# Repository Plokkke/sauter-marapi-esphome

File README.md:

# sauter-marapi-esphome

**Français** · [English](README.en.md)

Pilotez votre sèche-serviettes Sauter Marapi depuis Home Assistant, en gardant son écran et ses touches : une petite carte Wi-Fi se glisse sur le bus interne du radiateur.

> [!NOTE]
> **État du projet.** Le protocole du bus interne est décodé, et la carte MITM marche sur le radiateur (plaque d'essai, Wemos D1 mini, firmware ESPHome) : les touches et Home Assistant pilotent la carte de puissance. Restent la température, l'alimentation par la nappe, le circuit imprimé et le boîtier.

## Ce que ça permet

- **Suivre le radiateur** : consigne, Boost et arrêt réglés sur les touches, chauffe en cours.
- **Le régler depuis Home Assistant** : consigne, Boost (soufflerie), arrêt.
- **Garder l'appareil d'origine** : l'écran et les touches continuent de marcher comme avant ; le dernier qui parle, touche ou Home Assistant, a raison.
- **Rien à brancher sur le 230 V** : la carte s'alimente sur le 5 V de la nappe, comme le boîtier de commande.
- **Sans risque** : sans Home Assistant, les touches pilotent toujours le radiateur, et un Boost lancé par Home Assistant s'arrête de lui-même. Si la carte elle-même tombe en panne, le radiateur s'arrête (« Err 10 ») : il suffit de la débrancher et de reconnecter la nappe d'origine.

## Compatibilité

Étudié sur un **Sauter Marapi tactile 1750 W** (750 W de fluide et 1000 W de soufflerie), boîtier de commande `HM011 TD1N01 RAD`. Les sèche-serviettes et radiateurs du groupe Atlantic (Atlantic, Thermor, Sauter) qui affichent « Err 10 » quand leur nappe interne est débranchée utilisent probablement le même bus : à vérifier avec l'écoute de `discovery/`.

## Comment ça marche

Le radiateur a deux cartes, reliées par une nappe de trois fils (masse, 5 V, données) :

- le **boîtier de commande** (écran, touches tactiles) choisit la consigne, le mode et le Boost ;
- la **carte de puissance** chauffe le fluide et fait tourner la soufflerie, d'après sa propre sonde de température. Elle mène le dialogue : elle **appelle** le boîtier de commande plusieurs fois par seconde, et il répond par son état.

La carte coupe le fil de données et se place entre les deux, comme un intermédiaire (*man in the middle*). Elle a **son propre état** (arrêt, marche à une consigne, Boost), qu'elle donne à la carte de puissance en répondant à ses appels. Face au boîtier de commande, elle joue la carte de puissance : elle l'appelle et lit ses réponses. Les touches et Home Assistant changent cet état ; le dernier ordre gagne.

```mermaid
flowchart LR
  HA[Home Assistant] <-- Wi-Fi --> D1[Wemos D1 mini<br>ESPHome]
  CMD[Boîtier de commande<br>écran, touches] <-- données --> D1
  D1 <-- données --> PWR[Carte de puissance<br>fluide, soufflerie]
  PWR -. 5 V et masse, en direct .- CMD
  PWR -. 5 V .-> D1
```

**Limite** : le boîtier de commande n'accepte aucun ordre par le bus. Son écran affiche toujours ce qui a été réglé sur ses touches : un Boost lancé par Home Assistant ne s'y voit pas.

## Le bus interne en bref

Le détail, trame par trame, est dans [`knowledge/linap.md`](knowledge/linap.md).

- Un seul fil de données, **9 600 bauds, 7 bits et parité impaire**. Les trames font **5 octets** : un en-tête, 3 octets de données, puis leur XOR.
- La carte de puissance envoie `75`, `C7` et `61` en boucle (cycle de 305 ms). Après `75` et `C7`, elle envoie l'octet `46` seul : c'est l'appel. Le boîtier de commande répond **dans le bit qui suit**, par 3 octets et la somme de contrôle :

| Réponse à `46` | Sens |
|---|---|
| `B0 cc 80` | en marche, consigne = `cc` sans son bit 7, divisé par 2 |
| `38 80 80` | Boost |
| `80 80 80` | arrêt |

- La carte de puissance donne son état dans `C7` : `80 E0 38` au repos, `01 E0 38` en chauffe, `83 E0 98` en Boost, `80 E0 40` à l'arrêt.
- **La carte de puissance obéit à quiconque répond à temps** à ses appels. **Le boîtier de commande ne se laisse pas piloter** : il ne répond qu'aux appels `46` et `70`, et aucune des quelque 280 trames essayées n'a changé sa consigne ni son écran.

## La découverte du protocole

Aucune documentation n'existe sur ce bus. Il a été décodé avec un **Wemos D1 mini** branché sur la nappe, en trois étapes. Les firmwares, le schéma du banc et les outils sont dans [`discovery/`](discovery/README.md).

| Étape | L'ESP… | Résultat |
|---|---|---|
| 1. Écoute | écoute la nappe entre les deux cartes | format des trames, consigne, Boost, arrêt |
| 2. Fausse carte de puissance | appelle le boîtier de commande seul, sur table, sans secteur | il répond et donne tout ce qu'on fait sur ses touches, mais n'accepte aucun ordre |
| 3. Fausse carte de commande | répond à la carte de puissance, sur le radiateur | elle suit la consigne, le Boost et l'arrêt |

> [!WARNING]
> **Le bus interne est au potentiel du secteur.** Pendant les essais sur le radiateur, l'ESP flotte à ce potentiel : alimentation de laboratoire à sortie flottante, pilotage en Wi-Fi uniquement, jamais d'USB ni d'appareil relié à la terre. Couper le disjoncteur avant de toucher au montage. En cas de doute, faites appel à un électricien.

## Le matériel

> [!NOTE]
> En cours : la plaque d'essai ([`hardware/`](hardware/README.md)) marche sur le radiateur ; reste le circuit imprimé ([backlog](knowledge/backlog.md)).

Ce qui ne changera pas :

- **Un Wemos D1 mini** (ESP8266), firmware ESPHome avec un composant en C++ : la réponse aux appels part de nos propres interruptions. Son antenne imprimée tient la liaison sur le radiateur, là où un ESP32-C3 super mini la perdait.
- **Alimentée par la nappe**, en principe : le 5 V de la carte de puissance tient ≈ 160 mA en tout, et un D1 mini avec le boîtier de commande en prend ≈ 120 (VCC à 5,11 V, démarrages du radiateur et Boost validés pendant la découverte). Reste à le confirmer avec la carte MITM, essayée jusqu'ici sur une alimentation de labo. Un condensateur de 470 µF près de l'ESP absorbe les pointes du Wi-Fi.
- **Sur chaque voie**, le montage du banc : un pont diviseur pour lire DATA, un transistor NPN pour la tirer à la masse.
- **Toute la carte est au potentiel du secteur**, comme le boîtier de commande : elle doit être entièrement enfermée, sans rien de touchable, et se mettre à jour par Wi-Fi seulement.

## Firmware

Le firmware de la carte est une configuration **ESPHome** pour le D1 mini, avec un composant en C++, dans [`firmware/`](firmware/README.md) : logique des trames testée sur ordinateur, réponse aux appels sur interruption ; Wi-Fi, API Home Assistant et OTA par ESPHome.

```sh
uv tool install esphome
cp discovery/esphome/secrets.example.yaml discovery/esphome/secrets.yaml   # Wi-Fi, clé API, mot de passe OTA
firmware/tests/run.sh
esphome run firmware/sauter-marapi.yaml        # premier flash en USB, avant tout câblage ; ensuite OTA
```

Les firmwares du banc, eux, sont des configurations ESPHome pour D1 mini, dans `discovery/` :

```sh
esphome run discovery/1-sniffer/linap-sniffer.yaml       # premier flash en USB, avant tout câblage
esphome logs discovery/1-sniffer/linap-sniffer.yaml | discovery/tools/decode.py
```

## Dans Home Assistant

Par l'intégration ESPHome (détail : [`firmware/README.md`](firmware/README.md)) :

| Entité | Usage |
|---|---|
| Mode | `off`, `on`, `boost` : l'état de la carte, changé par les touches ou par Home Assistant |
| Setpoint | la consigne |
| Power board, Heating | ce que fait la carte de puissance : attente, chauffe, Boost, arrêt |
| Boost duration | durée d'un Boost lancé par Home Assistant (30 min par défaut) |

Le dernier ordre gagne : un ordre de Home Assistant remplace celui des touches, et le prochain changement fait aux touches le remplace à son tour. Au démarrage, la carte reprend l'état enregistré.

Le boîtier de commande n'envoie que sa consigne effective : en Éco, Home Assistant voit la consigne Éco, sans savoir que c'est l'Éco.

## Limites connues

- **Écran non synchronisé** : ce que Home Assistant impose n'apparaît pas à l'écran.
- **Pas de température** pour l'instant : la carte de puissance a sa sonde, et une capture longue cherche dans quelle trame passe la mesure.
- **Garantie** : ouvrir le boîtier de commande fait perdre la garantie (2 ans).

## Pour aller plus loin

- [`knowledge/linap.md`](knowledge/linap.md) : le bus interne, trame par trame.
- [`knowledge/architecture.md`](knowledge/architecture.md) : rôle de la carte, solution retenue, pistes écartées, sécurité.
- [`knowledge/backlog.md`](knowledge/backlog.md) : ce qui reste à faire.
- `knowledge/manuals/` : notice Sauter.

---

**Mots-clés** : Sauter Marapi tactile, sèche-serviettes soufflant, radiateur électrique, Groupe Atlantic, Thermor, Atlantic, bus interne, liaison Linap, Err 10, man in the middle, rétro-ingénierie, ESPHome, composant externe C++, Home Assistant, domotique, ESP8266, Wemos D1 mini, boîtier de commande `HM011 TD1N01 RAD`, `74 60 5004`, STM32F091CCT6, circuit imprimé KiCad.

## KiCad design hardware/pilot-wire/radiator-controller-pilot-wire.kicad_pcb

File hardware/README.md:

# Carte MITM

Un Wemos D1 mini (ESP8266) qui coupe le fil DATA de la nappe en deux : une voie vers la carte de puissance, une vers le boîtier de commande. VCC et GND traversent. Firmware : [`firmware/`](../firmware/sauter-marapi.yaml). Règles de dessin : [`CLAUDE.md`](../CLAUDE.md).

Révision 3 (11/11/2026) : le Wemos D1 mini remplace l'ESP32-C3 super mini, dont le Wi-Fi décrochait sur le radiateur ; ponts de lecture en 100 kΩ / 150 kΩ (révision 2). Le circuit imprimé viendra une fois la plaque validée sur le radiateur.

## Les blocs

| Bloc | Pièces | Rôle |
|---|---|---|
| Module | MOD1 sur J3 et J4 | Wemos D1 mini enfiché ; son antenne imprimée tient la liaison là où le C3 la perdait |
| Alimentation | C1 | le 5 V de la nappe passe de J1 à J2 et alimente le D1 ; C1 absorbe les pointes du Wi-Fi |
| Voie carte de puissance | J1, R1, R2, R3, R4, R5, Q1 | lecture par le pont R1/R2 sur D7 (GPIO13), émission par Q1 depuis D8 (GPIO15), rappel de DATA par R5 |
| Voie boîtier de commande | J2, R6, R7, R8, R9, Q2 | lecture par le pont R6/R7 sur D5 (GPIO14), émission par Q2 depuis D6 (GPIO12) ; le boîtier fait son propre rappel |

- **Pont diviseur** : 5,2 V × 150 kΩ / 250 kΩ ≈ 3,1 V sur l'entrée du D1, au-dessus de son seuil haut (≈ 2,5 V). **Il doit charger DATA le moins possible** : le seul rappel de DATA est celui du boîtier de commande, et le boîtier ne reconnaît plus les appels quand DATA retombe vers 4,1 V au repos. Mesuré au bureau le 11/11/2026 : aucune réponse avec 10 k + 15 k (25 kΩ), une sur quatre et tronquée avec 20 k + 30 k (50 kΩ), toutes avec 100 k + 150 k (250 kΩ). Le firmware n'active aucun rappel interne sur D5 et D7, sinon l'entrée ne descendrait plus assez bas.
- **Émission** : GPIO à l'état haut → NPN passant → DATA à la masse. Côté carte de puissance, l'UART0 (déplacée sur D7/D8) émet inversé ; côté boîtier de commande, D6 est piloté bit à bit par le timer1.
- **R4, R9** tiennent les NPN bloqués pendant le démarrage du D1. D8 (GPIO15) doit être bas au démarrage : R3 + R4 et le 10 kΩ du D1 l'y maintiennent. D3 et D4 (GPIO0, GPIO2) doivent être hauts au démarrage : ils ne peuvent pas commander un NPN.

## Nomenclature

| Repère | Valeur | Boîtier | LCSC |
|---|---|---|---|
| MOD1 | Wemos D1 mini (ESP8266) | module enfiché | — |
| J3, J4 | barrette femelle 1x8, pas de 2,54 | traversant | C27438 |
| J1, J2 | connecteur de nappe 3 points | à choisir (celui d'origine si possible) | à choisir |
| C1 | 470 µF 10 V | radial Ø 6,3 mm, pas de 2,5 mm | C43326 |
| R1, R6 | 100 kΩ 1 % 1/4 W | axial | C172965 |
| R2, R7 | 150 kΩ 1 % 1 W (pas de 1/4 W trouvée chez LCSC) | axial, 9 mm | C119513 |
| R3, R4, R8, R9 | 10 kΩ 1 % 1/4 W | axial | C57436 |
| R5 | 4,7 kΩ 5 % 1/4 W | axial | C1364279 |
| Q1, Q2 | 2N3904 | TO-92 (E-B-C, face plate vers soi) | C2874602 |

## Câbler la plaque d'essai

Sur le radiateur, **toute la carte est au potentiel du secteur** : disjoncteur coupé pour câbler, firmware flashé en USB avant tout câblage, jamais d'USB ensuite.

1. **Voie carte de puissance seule** (J1), boîtier de commande débranché : comme l'étape 3 de `discovery/`. Home Assistant passe « Mode » sur `on` puis `boost` ; « Power board polls answered » doit rester à 100 %. Mesurer ensuite la marge (« Reply gap ») et la consommation sur la nappe.
2. **MITM complet** : boîtier de commande sur J2. « Commander polls answered » doit rester à 100 % ; vérifier que les touches changent l'état et que le dernier ordre gagne, puis allumer « Frame log » pour l'analyse.

## Régénérer

```sh
hardware/scripts/check.sh   # régénère le schéma, ERC sans violation, exporte linap-mitm.svg
```

Le schéma est produit par [`scripts/generate-schematic.py`](scripts/generate-schematic.py) : on le modifie là, pas dans KiCad. Le module partagé [`scripts/kicad_sheet.py`](scripts/kicad_sheet.py) sert aussi au schéma du banc (`discovery/bench/`).

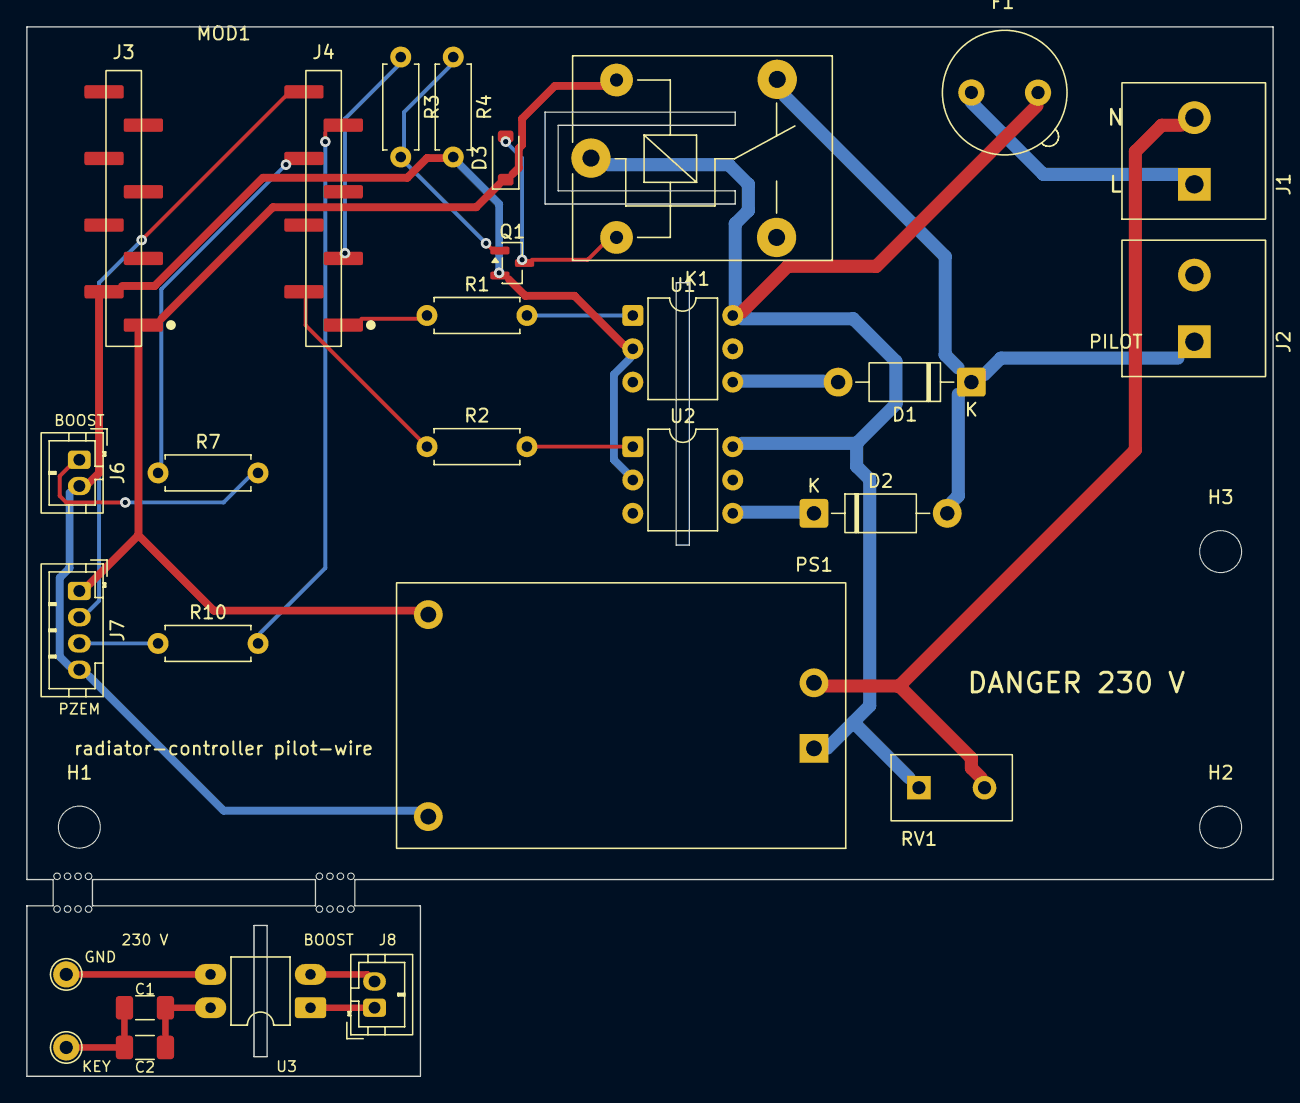
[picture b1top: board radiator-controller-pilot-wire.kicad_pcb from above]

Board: 2 copper layers, 95.0 x 80.0 mm, 34 parts (0 on the bottom side), 25 nets.

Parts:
C1, C2: 10-100p C0G; C_1206_3216Metric_Pad1.33x1.80mm_HandSolder
D1, D2: 1N4007; D_DO-41_SOD81_P10.16mm_Horizontal
D3: 1N4148W; D_SOD-123
F1: TR5 holder + T1A fuse; Fuseholder_TR5_Littelfuse_No560_No460
H1, H2, H3: MountingHole_3.2mm_M3
J1: KF128-5.08 (L, N); TerminalBlock_Kefa_KF128-5.08_1x02
J2: KF128-5.08 (pilot wire); TerminalBlock_Kefa_KF128-5.08_1x02
J3, J4: Socket 1x8 SMD; PinSocket_1x08_P2.54mm_SMD_HX-ZQ
J6: JST PH 2 (Boost photoMOS LED); JST_PH_B2B-PH-K_1x02_P2.00mm_Vertical_Drill0.9
J7: JST PH 4 (PZEM-004T v3: 5V RX TX GND); JST_PH_B4B-PH-K_1x04_P2.00mm_Vertical_Drill0.9
J8: JST PH 2 (from J6); JST_PH_B2B-PH-K_1x02_P2.00mm_Vertical_Drill0.9
K1: SRD-05VDC-SL-C; Relay_SPDT_SANYOU_SRD_Series_Form_C
MB1, MB2: Breakaway_MouseBites_3mm
MOD1: ESP32-C3 super mini; ESP32-C3_SuperMini_Outline
PS1: HLK-PM01; Converter_ACDC_HLK-PM01
Q1: MMBT2222A; SOT-23
R1, R2, R7: 220; R_Axial_DIN0207_L6.3mm_D2.5mm_P7.62mm_Horizontal
R3, R10: 1k; R_Axial_DIN0207_L6.3mm_D2.5mm_P7.62mm_Horizontal
R4: 10k; R_Axial_DIN0207_L6.3mm_D2.5mm_P7.62mm_Horizontal
RV1: MOV-07D431K (275VAC); RV_Disc_D9mm_W4.8mm_P5mm_Inline
TP1: KEY; TestPoint_THTPad_D2.0mm_Drill1.0mm
TP2: CTRL GND; TestPoint_THTPad_D2.0mm_Drill1.0mm
U1, U2: MOC3043M; DIP-6_W7.62mm
U3: photoMOS; DIP-4_W7.62mm_LongPads

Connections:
+5V: D3.1, J3.1, J7.1, K1.5, PS1.4
/GPIO5: J4.1, R1.1
/GPIO6: J4.2, R2.1
/GPIO7: J4.3, R3.1
/GPIO10: J4.6, R7.1
/GPIO20: J4.7, R10.2
/GPIO21: J4.8, J7.2
/KEY: C1.2, C2.2, TP1.1
/KEY_SW: C1.1, C2.1, U3.4
/L: F1.1, J1.1
/LINAP_GND: TP2.1, U3.3
/L_FUSED: F1.2, K1.1, PS1.1, RV1.1, U1.6, U2.6
/N: J1.2, PS1.2, RV1.2
/PILOT_WIRE: D1.1, D2.2, J2.1, K1.4
/U1_OUT: D1.2, U1.4
/U2_OUT: D2.1, U2.4
GND: J3.2, J6.2, J7.4, PS1.3, Q1.2, R4.2, U1.2, U2.2
unnamed: D3.2, K1.2, Q1.3
unnamed: J6.1, R7.2
unnamed: J7.3, R10.1
unnamed: J8.1, U3.1
unnamed: J8.2, U3.2
unnamed: Q1.1, R3.2, R4.1
unnamed: R1.2, U1.1
unnamed: R2.2, U2.1

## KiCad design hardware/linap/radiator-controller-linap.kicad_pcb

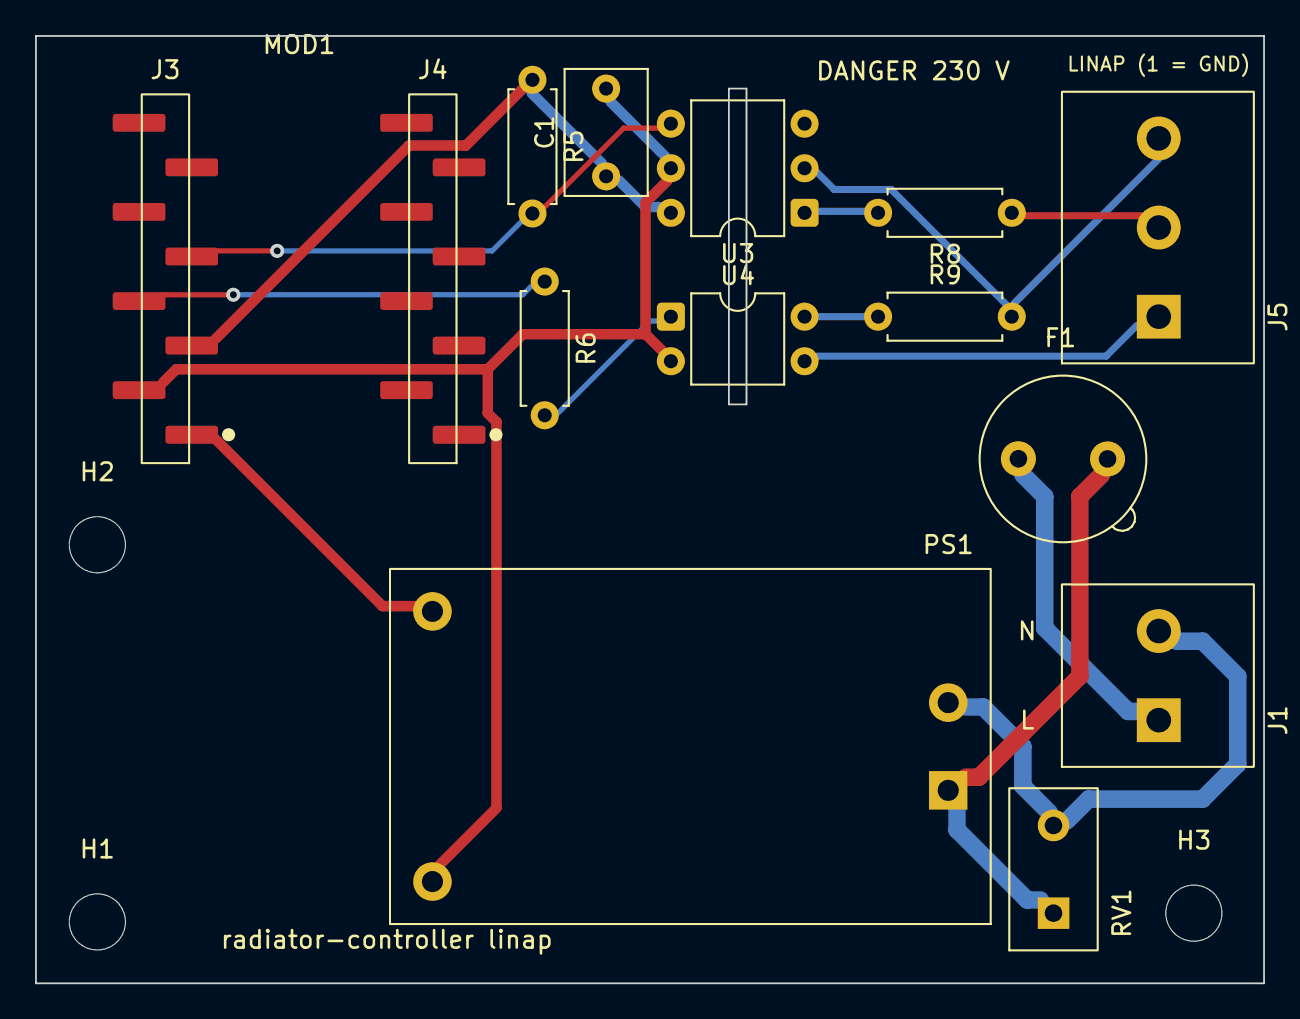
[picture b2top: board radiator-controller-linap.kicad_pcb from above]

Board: 2 copper layers, 70.0 x 54.0 mm, 18 parts (0 on the bottom side), 14 nets.

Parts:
C1: 100n; C_Rect_L7.0mm_W4.5mm_P5.00mm
F1: TR5 holder + T1A fuse; Fuseholder_TR5_Littelfuse_No560_No460
H1, H2, H3: MountingHole_3.2mm_M3
J1: KF128-5.08 (L, N); TerminalBlock_Kefa_KF128-5.08_1x02
J3, J4: Socket 1x8 SMD; PinSocket_1x08_P2.54mm_SMD_HX-ZQ
J5: KF128-5.08 (Linap GND, VCC, DATA); TerminalBlock_Kefa_KF128-5.08_1x03
MOD1: ESP32-C3 super mini; ESP32-C3_SuperMini_Outline
PS1: HLK-PM01; Converter_ACDC_HLK-PM01
R5: 1k; R_Axial_DIN0207_L6.3mm_D2.5mm_P7.62mm_Horizontal
R6: 220; R_Axial_DIN0207_L6.3mm_D2.5mm_P7.62mm_Horizontal
R8: TBD; R_Axial_DIN0207_L6.3mm_D2.5mm_P7.62mm_Horizontal
R9: 100; R_Axial_DIN0207_L6.3mm_D2.5mm_P7.62mm_Horizontal
RV1: MOV-07D431K (275VAC); RV_Disc_D9mm_W4.8mm_P5mm_Inline
U3: H11L1M; DIP-6_W7.62mm
U4: LTV-817; DIP-4_W7.62mm

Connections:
+3V3: C1.1, J3.3, R5.1, U3.6
+5V: J3.1, PS1.4
/GPIO3: J3.5, R5.2, U3.4
/GPIO4: J3.4, R6.1
/L: F1.1, J1.1
/LINAP_DATA: J5.3, R9.2, U3.2
/LINAP_GND: J5.1, U4.3
/LINAP_LED: R8.2, U3.1
/LINAP_TX: R9.1, U4.4
/LINAP_VCC: J5.2, R8.1
/L_FUSED: F1.2, PS1.1, RV1.1
/N: J1.2, PS1.2, RV1.2
GND: C1.2, J3.2, PS1.3, U3.5, U4.2
unnamed: R6.2, U4.1

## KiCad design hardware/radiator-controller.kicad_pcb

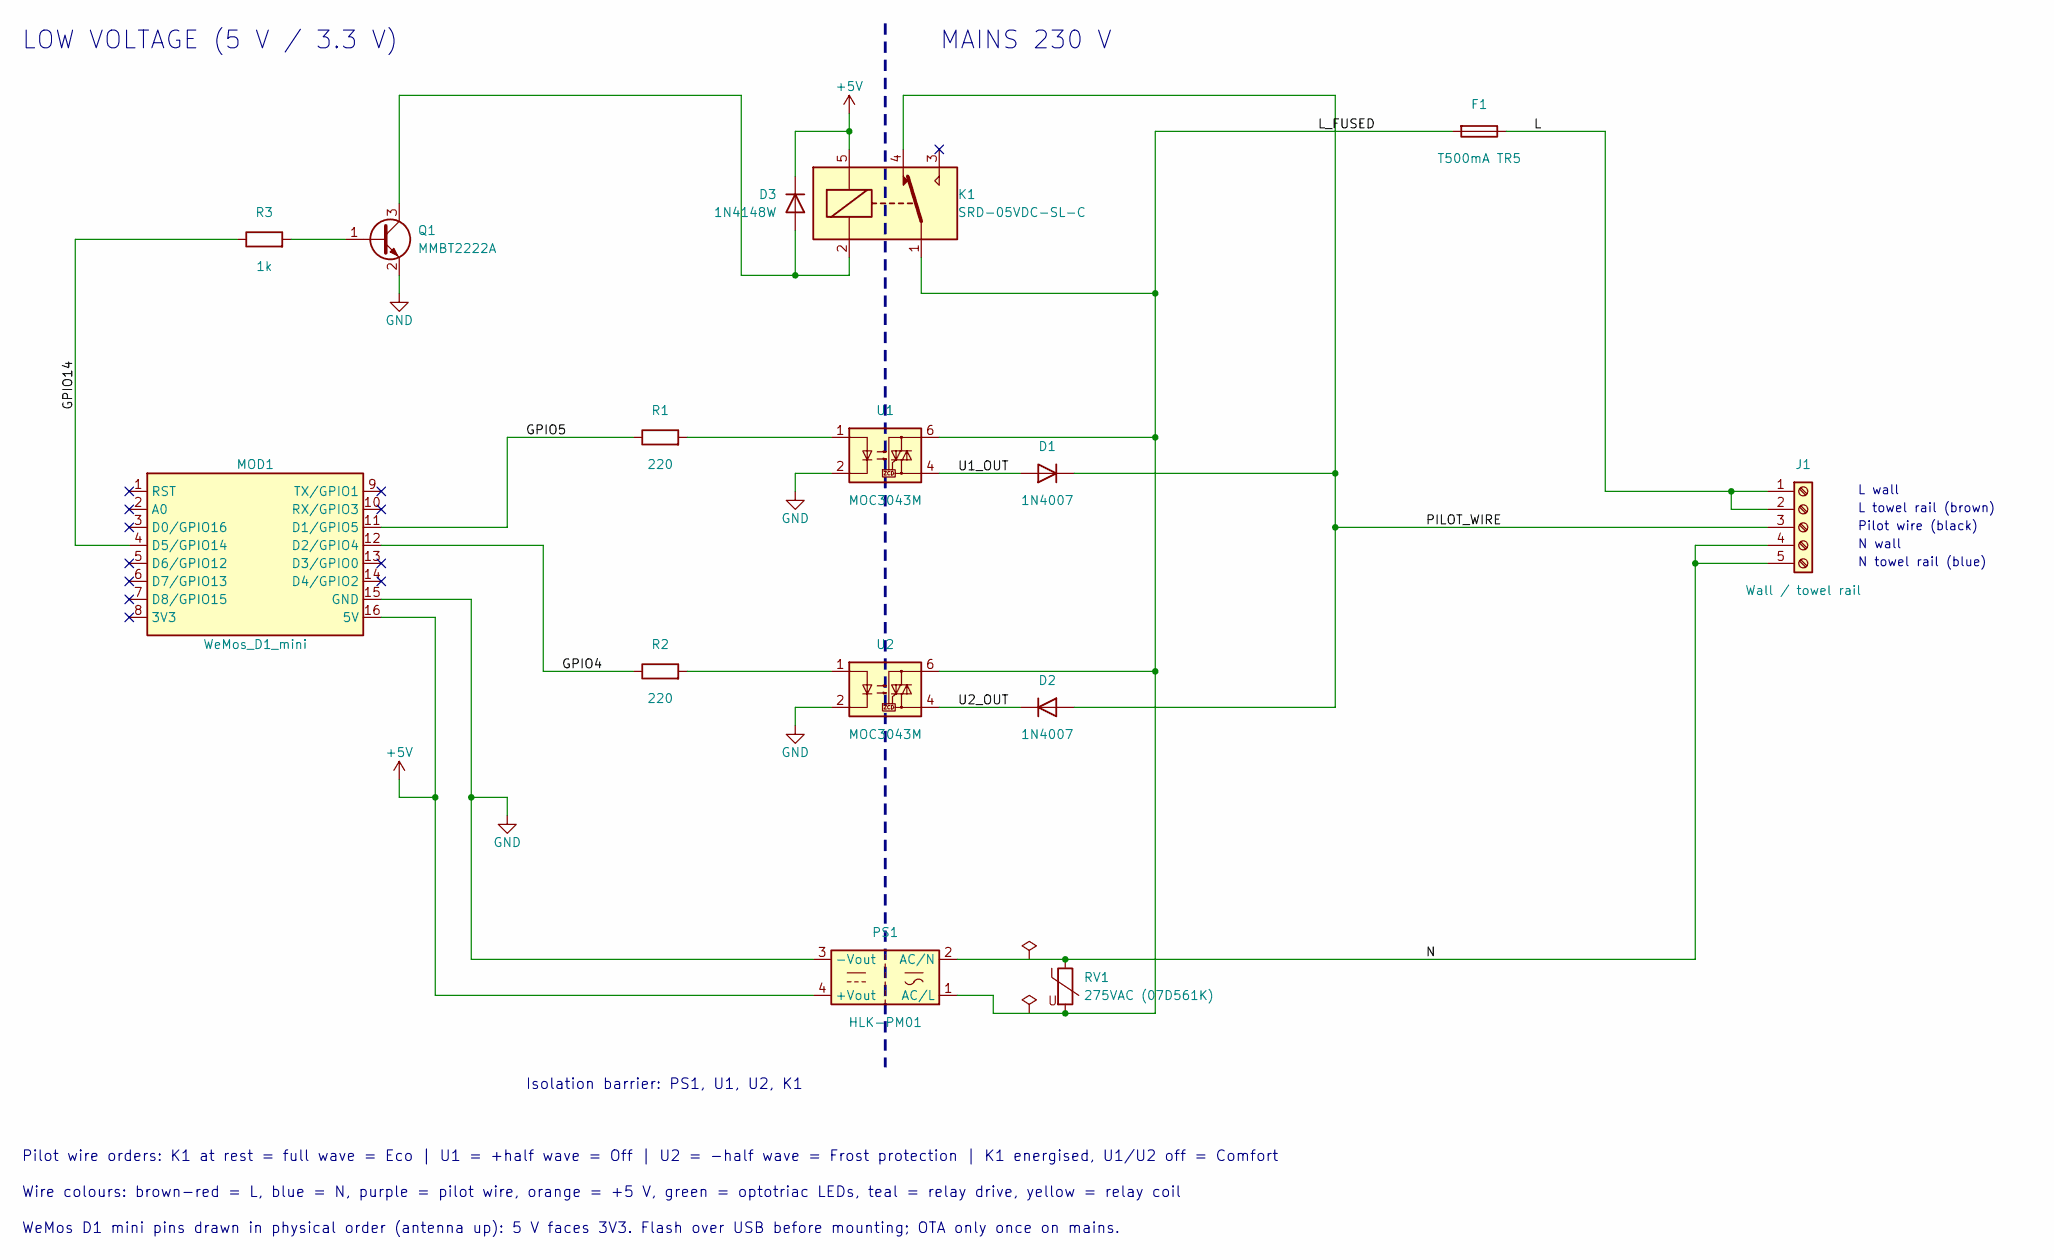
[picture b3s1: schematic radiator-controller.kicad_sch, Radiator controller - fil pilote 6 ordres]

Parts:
D1, D2: 1N4007; D_DO-41_SOD81_P10.16mm_Horizontal
D3: 1N4148W; D_SOD-123
F1: T500mA TR5; Fuseholder_TR5_Littelfuse_No560_No460
J1: Wall / towel rail; TerminalBlock_Phoenix_MKDS-1,5-5-5.08_1x05_P5.08mm_Horizont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
K1: SRD-05VDC-SL-C; Relay_SPDT_SANYOU_SRD_Series_Form_C
MOD1: WeMos_D1_mini; WEMOS_D1_mini_SMD_sockets
PS1: HLK-PM01; Converter_ACDC_Hi-Link_HLK-PMxx
Q1: MMBT2222A; SOT-23
R1, R2: 220; R_0805_2012Metric
R3: 1k; R_0805_2012Metric
RV1: 275VAC (07D561K); RV_Disc_D9mm_W4.1mm_P5mm
U1, U2: MOC3043M; DIP-6_W7.62mm

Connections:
+5V: D3.1 (K), K1.5, MOD1.16 (5V), PS1.4 (+Vout)
/GPIO4: MOD1.12 (D2/GPIO4), R2.1
/GPIO5: MOD1.11 (D1/GPIO5), R1.1
/GPIO14: MOD1.4 (D5/GPIO14), R3.1
/L: F1.1, J1.1, J1.2
/L_FUSED: F1.2, K1.1, PS1.1 (AC/L), RV1.2, U1.6, U2.6
/N: J1.4, J1.5, PS1.2 (AC/N), RV1.1
/PILOT_WIRE: D1.1 (K), D2.2 (A), J1.3, K1.4
/U1_OUT: D1.2 (A), U1.4
/U2_OUT: D2.1 (K), U2.4
GND: MOD1.15 (GND), PS1.3 (-Vout), Q1.2 (E), U1.2, U2.2
unnamed: D3.2 (A), K1.2, Q1.3 (C)
unnamed: Q1.1 (B), R3.2
unnamed: R1.2, U1.1
unnamed: R2.2, U2.1

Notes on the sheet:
LOW VOLTAGE (5 V / 3.3 V)
MAINS 230 V
Isolation barrier: PS1, U1, U2, K1
Pilot wire orders: K1 at rest = full wave = Eco | U1 = +half wave = Off | U2 = -half wave = Frost protection | K1 energised, U1/U2 off = Comfort
Wire colours: brown-red = L, blue = N, purple = pilot wire, orange = +5 V, green = optotriac LEDs, teal = relay drive, yellow = relay coil
WeMos D1 mini pins drawn in physical order (antenna up): 5 V faces 3V3. Flash over USB before mounting; OTA only once on mains.
L wall
L towel rail (brown)
Pilot wire (black)
N wall
N towel rail (blue)

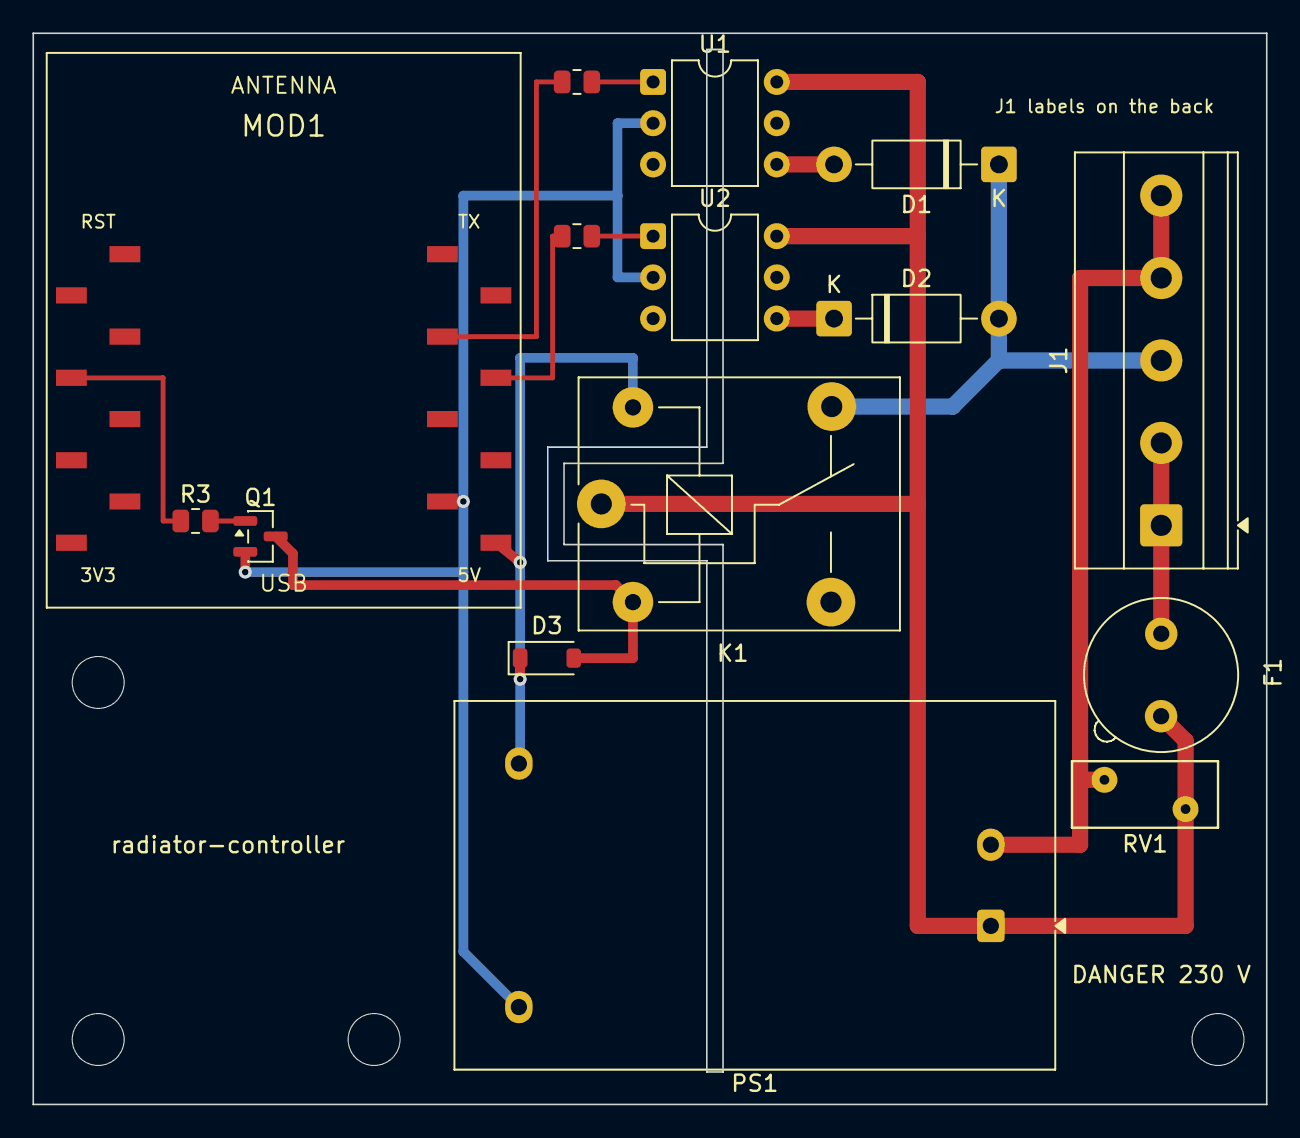
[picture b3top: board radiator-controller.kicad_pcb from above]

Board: 2 copper layers, 76.0 x 66.0 mm, 19 parts (0 on the bottom side), 15 nets.

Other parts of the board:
H1, H2, H3, H4: MountingHole_3.2mm_M3

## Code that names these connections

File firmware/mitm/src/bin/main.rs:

//! ESP32-C3 in the middle of the Linap bus (`knowledge/architecture.md`): owns the radiator's state, which the keys
//! and Home Assistant (over MQTT) change, and gives it to the power board.
#![no_std]
#![no_main]
#![deny(clippy::mem_forget, reason = "mem::forget is generally not safe with esp_hal types")]

use embassy_executor::Spawner;
use esp_backtrace as _;
use esp_hal::clock::CpuClock;
use esp_hal::gpio::Flex;
use esp_hal::timer::timg::TimerGroup;
use esp_storage::FlashStorage;
use log::info;
use mitm::bus::{self, Half};
use mitm::{console, mqtt, network, ota};

extern crate alloc;

esp_bootloader_esp_idf::esp_app_desc!();

#[allow(clippy::large_stack_frames, reason = "buffers are allocated in main")]
#[esp_rtos::main]
async fn main(spawner: Spawner) -> ! {
    esp_println::logger::init_logger_from_env();
    let peripherals = esp_hal::init(esp_hal::Config::default().with_cpu_clock(CpuClock::max()));
    esp_alloc::heap_allocator!(#[esp_hal::ram(reclaimed)] size: 66320);
    esp_alloc::heap_allocator!(size: 36 * 1024);
    let timg0 = TimerGroup::new(peripherals.TIMG0);
    esp_rtos::start(timg0.timer0, peripherals.FROM_CPU_INTR0);

    // Pins: see the MITM schematic. TX drives the NPN that pulls DATA low, hence inverted in bus.rs.
    bus::start(
        Half { uart: peripherals.UART0, rx: Flex::new(peripherals.GPIO4), tx: Flex::new(peripherals.GPIO5) },
        Half { uart: peripherals.UART1, rx: Flex::new(peripherals.GPIO6), tx: Flex::new(peripherals.GPIO7) },
    );
    info!("Linap bus served");
    console::start(spawner, peripherals.USB_DEVICE);

    let mut flash = FlashStorage::new(peripherals.FLASH);
    ota::confirm_running_image(&mut flash);

    let stack = network::start(spawner, peripherals.WIFI);
    spawner.spawn(ota::serve(stack, flash).expect("OTA task"));
    spawner.spawn(mqtt::run(stack).expect("mqtt task"));
    spawner.spawn(mqtt::expire_boost().expect("expiry task"));
    spawner.spawn(mitm::command_side::play_power_board().expect("command side task"));
    loop {
        embassy_time::Timer::after_secs(3600).await;
    }
}
